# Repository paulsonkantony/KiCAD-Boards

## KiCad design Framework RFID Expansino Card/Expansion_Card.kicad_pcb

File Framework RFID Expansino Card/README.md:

# RFID Reader Expansion
This expansion will allow the user to add a RFID reader to the Framework Laptop (frame.work)

Framework Expansion Card Template is licensed under CC BY 4.0
- https://github.com/FrameworkComputer/ExpansionCards

USB RFID Reader schematic is released by Sparkfun under CC BY-SA 3.0
- https://github.com/sparkfun/RFID_USB_Reader/tree/V_1.8

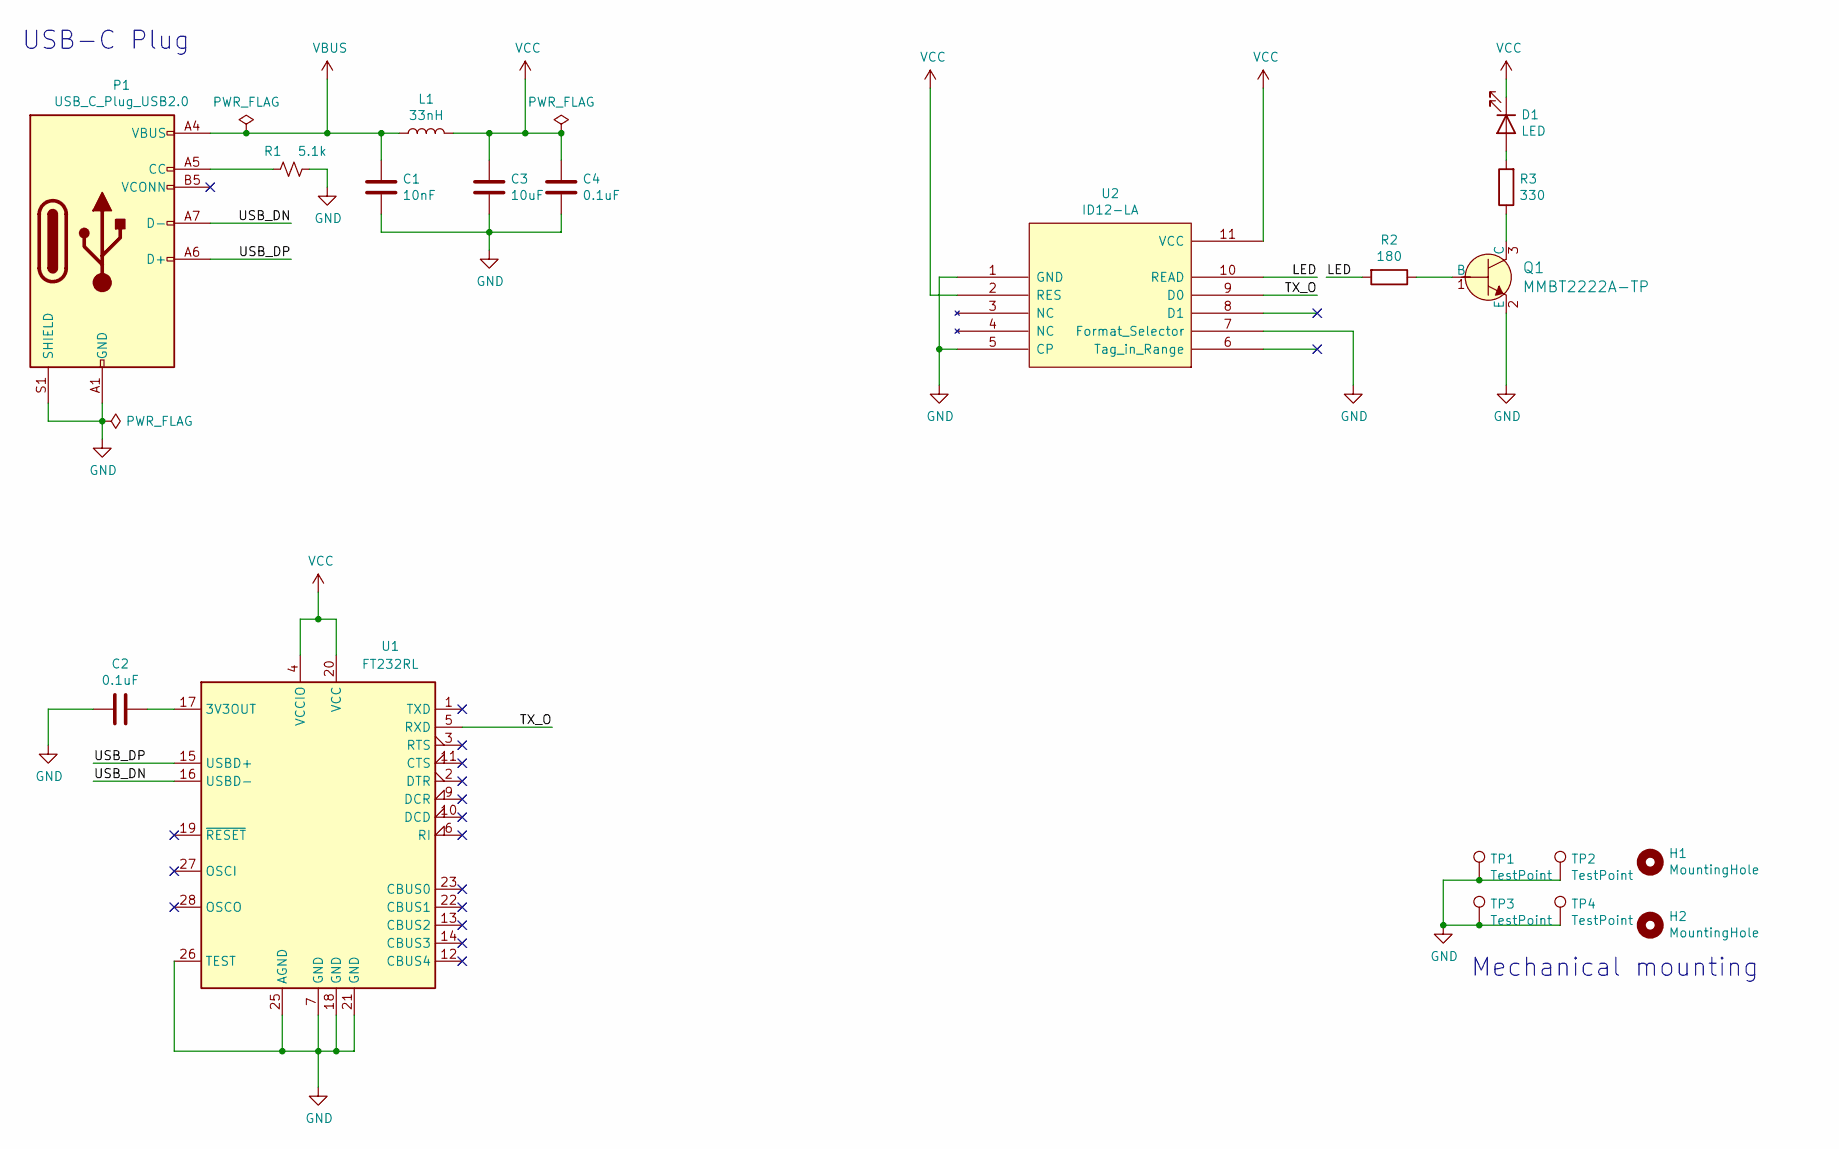
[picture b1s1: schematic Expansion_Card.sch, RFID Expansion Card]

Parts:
C1: 10nF; C_0805_2012Metric_Pad1.18x1.45mm_HandSolder
C2, C4: 0.1uF; C_0805_2012Metric_Pad1.18x1.45mm_HandSolder
C3: 10uF; C_0805_2012Metric_Pad1.18x1.45mm_HandSolder
D1: LED; LED_0805_2012Metric_Pad1.15x1.40mm_HandSolder
H1, H2: MountingHole; MountingHole_2.2mm_M2
L1: 33nH; L_0805_2012Metric_Pad1.15x1.40mm_HandSolder
P1: USB_C_Plug_USB2.0; USB_C_Plug_Molex_105444
Q1: MMBT2222A-TP; SOT-23-3; MPN MMBT2222A-TP; Digi-Key_PN MMBT2222ATPMSCT-ND
R1: 5.1k; R_0805_2012Metric_Pad1.20x1.40mm_HandSolder
R2: 180; R_0805_2012Metric_Pad1.20x1.40mm_HandSolder
R3: 330; R_0805_2012Metric_Pad1.20x1.40mm_HandSolder
TP1, TP2, TP3, TP4: TestPoint; TestPoint_Pad_1.5x1.5mm
U1: FT232RL; SSOP-28_5.3x10.2mm_P0.65mm
U2: ID12-LA; ID-12LA

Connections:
/LED: R2.2, U2.10 (READ)
/TX_O: U1.5 (RXD), U2.9 (D0)
/USB_DN: P1.A7 (D-), U1.16 (USBD-)
/USB_DP: P1.A6 (D+), U1.15 (USBD+)
GND: C1.2, C2.2, C3.2, C4.2, P1.A1 (GND), P1.A12 (GND), P1.B1 (GND), P1.B12 (GND), P1.S1 (SHIELD), Q1.2 (E), R1.2, TP1.1, TP2.1, TP3.1, TP4.1, U1.7 (GND), U1.18 (GND), U1.21 (GND), U1.25 (AGND), U1.26 (TEST), U2.1 (GND), U2.5 (CP), U2.7 (Format_Selector)
unnamed: C2.1, U1.17 (3V3OUT)
unnamed: D1.2 (A), R3.2
unnamed: P1.A5 (CC), R1.1
unnamed: Q1.1 (B), R2.1
unnamed: Q1.3 (C), R3.1
VBUS: C1.1, L1.1, P1.A4 (VBUS), P1.A9 (VBUS), P1.B4 (VBUS), P1.B9 (VBUS)
VCC: C3.1, C4.1, D1.1 (K), L1.2, U1.4 (VCCIO), U1.20 (VCC), U2.2 (RES), U2.11 (VCC)

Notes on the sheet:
USB-C Plug
Mechanical mounting

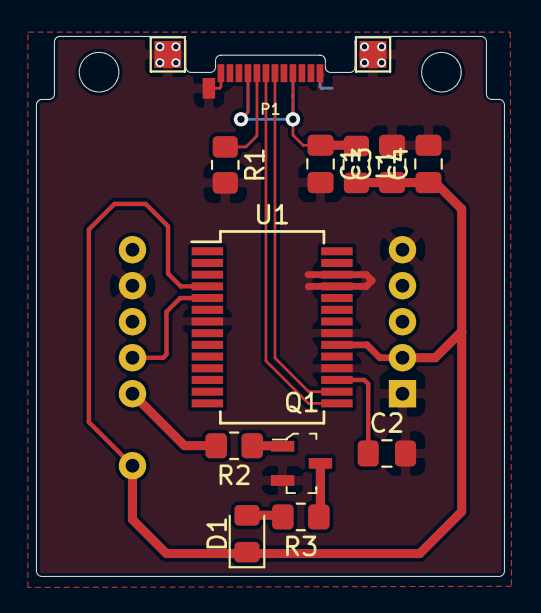
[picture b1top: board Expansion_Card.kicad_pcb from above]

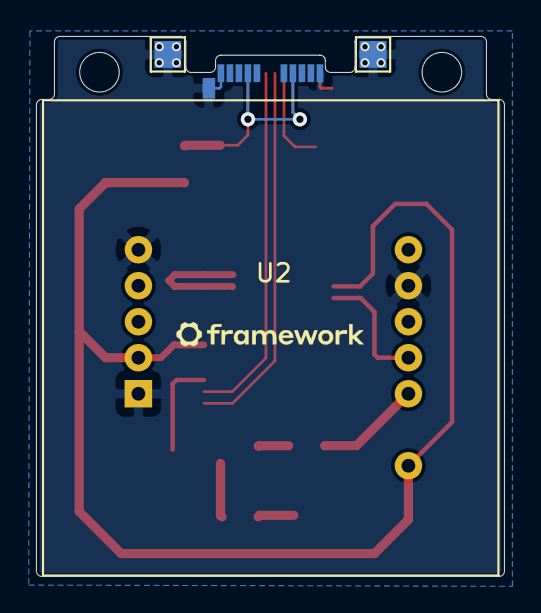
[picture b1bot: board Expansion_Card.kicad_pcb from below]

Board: 2 copper layers, 26.0 x 30.0 mm, 19 parts (3 on the bottom side), 12 nets.

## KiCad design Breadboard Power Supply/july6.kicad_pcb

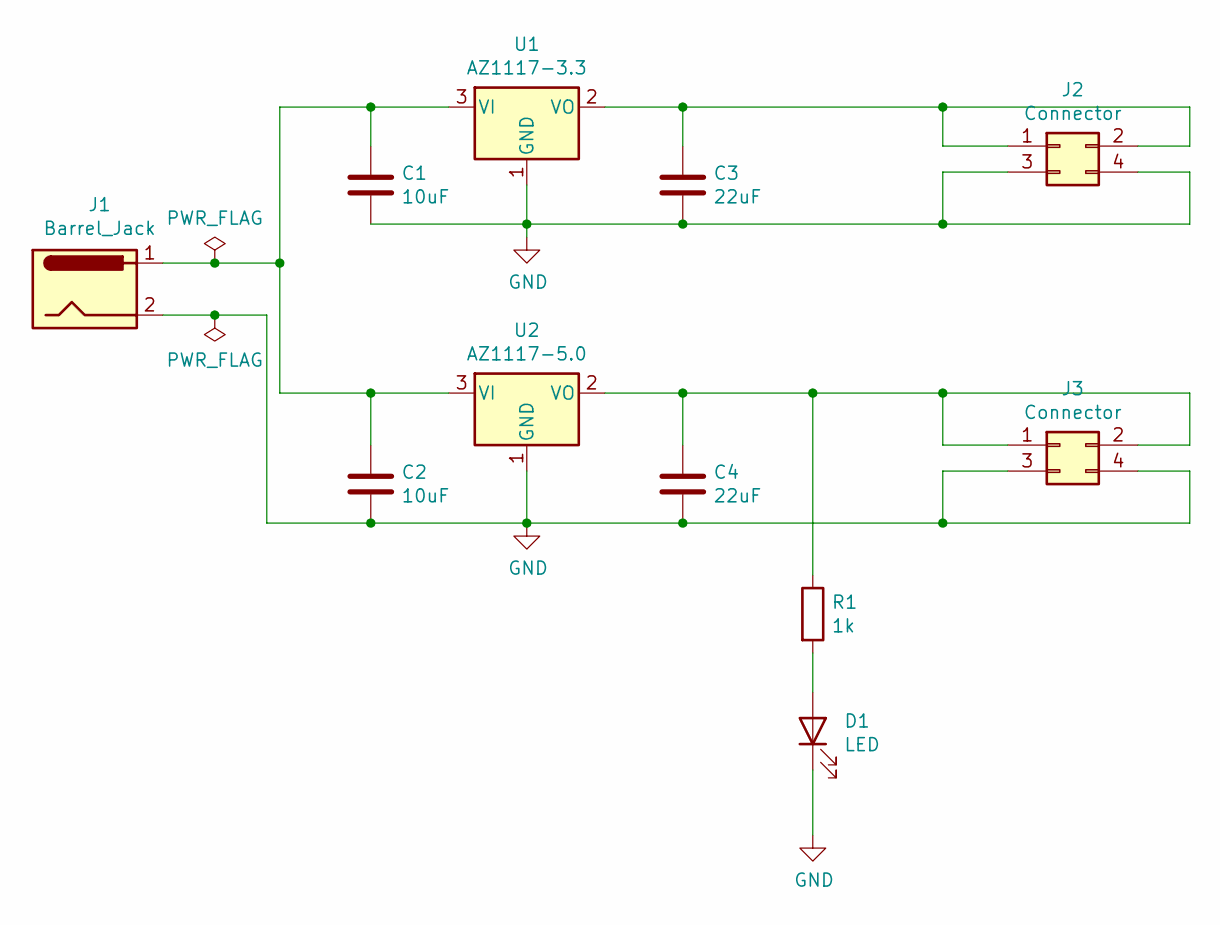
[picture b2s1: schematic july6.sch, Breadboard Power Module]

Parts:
C1, C2: 10uF; C_0805_2012Metric_Pad1.18x1.45mm_HandSolder
C3, C4: 22uF; C_0805_2012Metric_Pad1.18x1.45mm_HandSolder
D1: LED; LED_D3.0mm
J1: Barrel_Jack; BarrelJack_CUI_PJ-102AH_Horizontal
J2, J3: Connector; PinHeader_2x02_P2.54mm_Vertical
R1: 1k; R_0805_2012Metric_Pad1.20x1.40mm_HandSolder
U1: AZ1117-3.3; SOT-223-3_TabPin2
U2: AZ1117-5.0; SOT-223-3_TabPin2

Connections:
GND: C1.2, C2.2, C3.2, C4.2, D1.1 (K), J1.2, J2.3, J2.4, J3.3, J3.4, U1.1 (GND), U2.1 (GND)
unnamed: C1.1, C2.1, J1.1, U1.3 (VI), U2.3 (VI)
unnamed: C3.1, J2.1, J2.2, U1.2 (VO)
unnamed: C4.1, J3.1, J3.2, R1.1, U2.2 (VO)
unnamed: D1.2 (A), R1.2

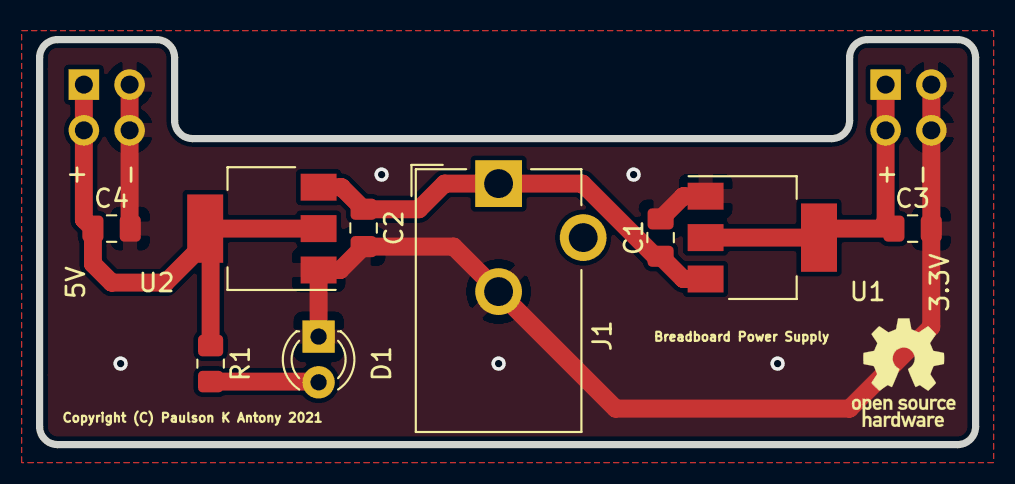
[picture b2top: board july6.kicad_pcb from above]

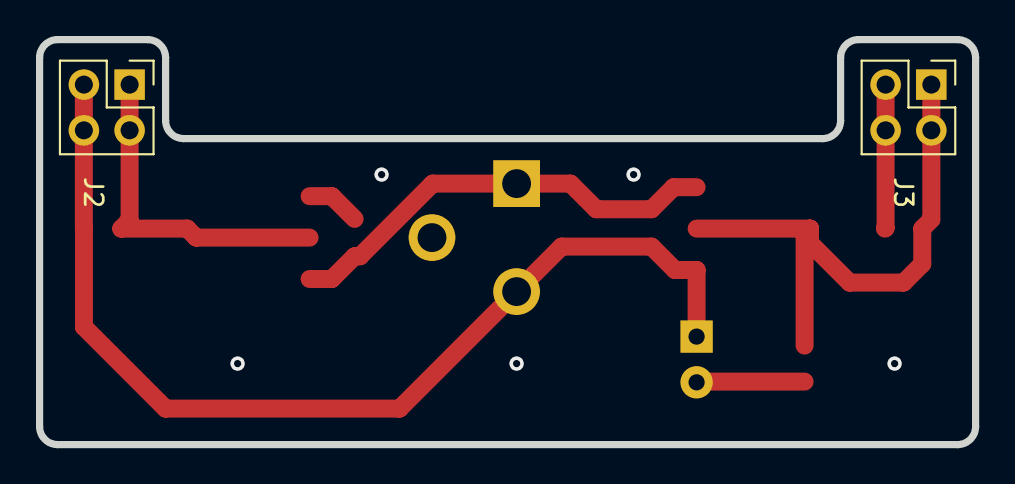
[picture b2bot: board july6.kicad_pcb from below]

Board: 2 copper layers, 52.0 x 22.5 mm, 11 parts (2 on the bottom side), 5 nets.

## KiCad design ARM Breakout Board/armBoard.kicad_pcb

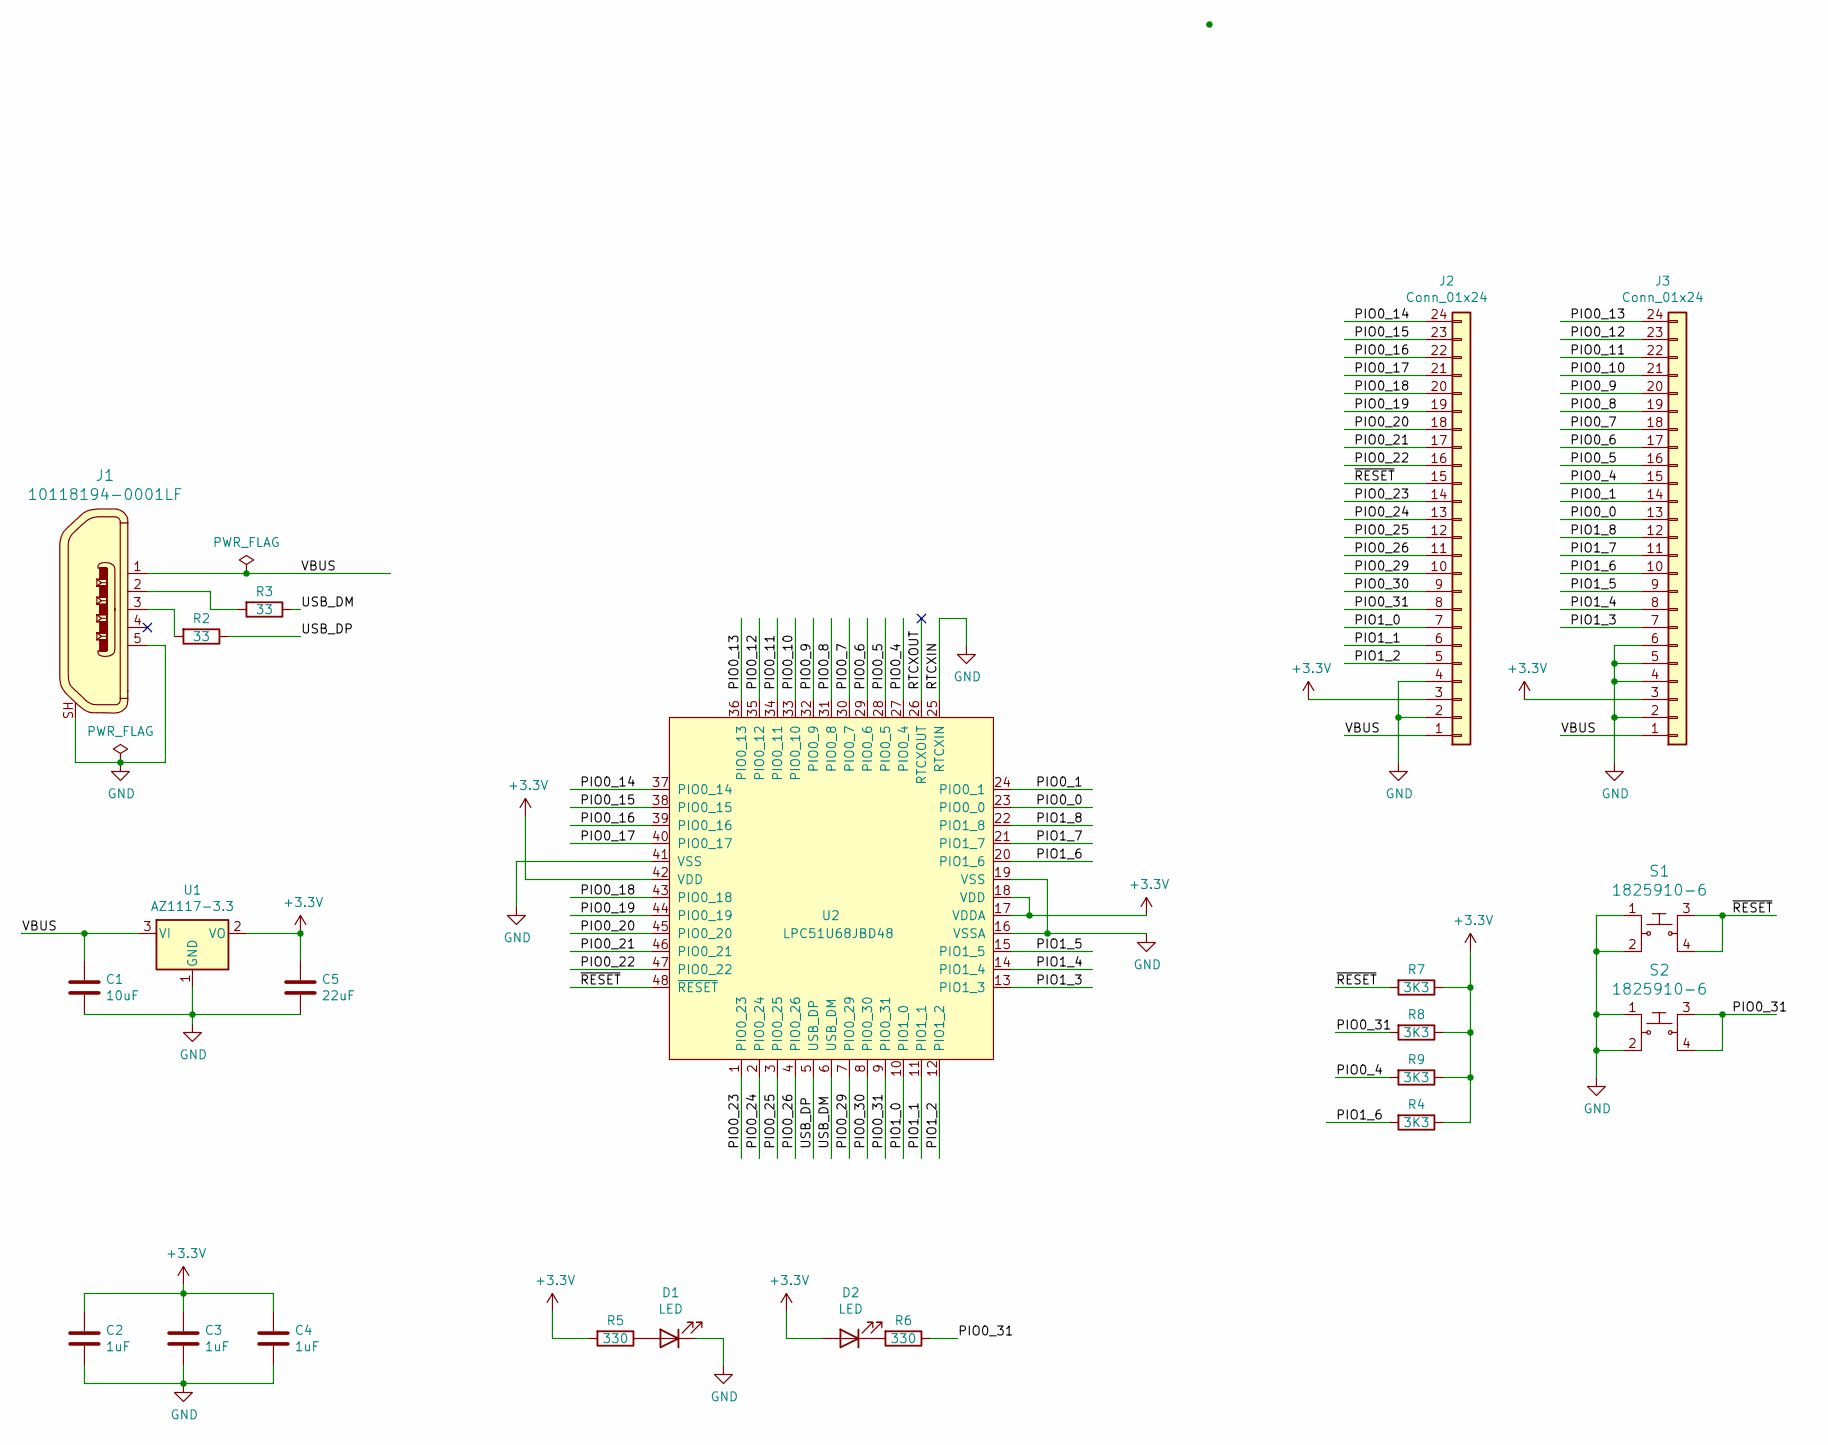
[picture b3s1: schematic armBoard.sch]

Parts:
C1: 10uF; C_0805_2012Metric_Pad1.18x1.45mm_HandSolder
C2, C3, C4: 1uF; C_0805_2012Metric_Pad1.18x1.45mm_HandSolder
C5: 22uF; C_0805_2012Metric_Pad1.18x1.45mm_HandSolder
D1, D2: LED; LED_0805_2012Metric_Pad1.15x1.40mm_HandSolder
J1: 10118194-0001LF; USB_Micro_B_Female_10118194-0001LF; MPN 10118194-0001LF; Digi-Key_PN 609-4618-1-ND
J2, J3: Conn_01x24; PinHeader_1x24_P2.54mm_Vertical
R2, R3: 33; R_0805_2012Metric_Pad1.20x1.40mm_HandSolder
R4, R7, R8, R9: 3K3; R_0805_2012Metric_Pad1.20x1.40mm_HandSolder
R5, R6: 330; R_0805_2012Metric_Pad1.20x1.40mm_HandSolder
S1, S2: 1825910-6; Switch_Tactile_THT_6x6mm; MPN 1825910-6; Digi-Key_PN 450-1650-ND
U1: AZ1117-3.3; SOT-223-3_TabPin2
U2: LPC51U68JBD48; LQFP-48_7x7mm_P0.5mm

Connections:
+3V3: C2.1, C3.1, C4.1, C5.1, D2.2 (A), J2.3, J3.3, R4.1, R5.2, R7.1, R8.1, R9.1, U1.2 (VO), U2.17 (VDDA), U2.18 (VDD), U2.42 (VDD)
/PIO0_0: J3.13, U2.23 (PIO0_0)
/PIO0_1: J3.14, U2.24 (PIO0_1)
/PIO0_4: J3.15, R9.2, U2.27 (PIO0_4)
/PIO0_5: J3.16, U2.28 (PIO0_5)
/PIO0_6: J3.17, U2.29 (PIO0_6)
/PIO0_7: J3.18, U2.30 (PIO0_7)
/PIO0_8: J3.19, U2.31 (PIO0_8)
/PIO0_9: J3.20, U2.32 (PIO0_9)
/PIO0_10: J3.21, U2.33 (PIO0_10)
/PIO0_11: J3.22, U2.34 (PIO0_11)
/PIO0_12: J3.23, U2.35 (PIO0_12)
/PIO0_13: J3.24, U2.36 (PIO0_13)
/PIO0_14: J2.24, U2.37 (PIO0_14)
/PIO0_15: J2.23, U2.38 (PIO0_15)
/PIO0_16: J2.22, U2.39 (PIO0_16)
/PIO0_17: J2.21, U2.40 (PIO0_17)
/PIO0_18: J2.20, U2.43 (PIO0_18)
/PIO0_19: J2.19, U2.44 (PIO0_19)
/PIO0_20: J2.18, U2.45 (PIO0_20)
/PIO0_21: J2.17, U2.46 (PIO0_21)
/PIO0_22: J2.16, U2.47 (PIO0_22)
/PIO0_23: J2.14, U2.1 (PIO0_23)
/PIO0_24: J2.13, U2.2 (PIO0_24)
/PIO0_25: J2.12, U2.3 (PIO0_25)
/PIO0_26: J2.11, U2.4 (PIO0_26)
/PIO0_29: J2.10, U2.7 (PIO0_29)
/PIO0_30: J2.9, U2.8 (PIO0_30)
/PIO0_31: J2.8, R6.1, R8.2, S2.3, S2.4, U2.9 (PIO0_31)
/PIO1_0: J2.7, U2.10 (PIO1_0)
/PIO1_1: J2.6, U2.11 (PIO1_1)
/PIO1_2: J2.5, U2.12 (PIO1_2)
/PIO1_3: J3.7, U2.13 (PIO1_3)
/PIO1_4: J3.8, U2.14 (PIO1_4)
/PIO1_5: J3.9, U2.15 (PIO1_5)
/PIO1_6: J3.10, R4.2, U2.20 (PIO1_6)
/PIO1_7: J3.11, U2.21 (PIO1_7)
/PIO1_8: J3.12, U2.22 (PIO1_8)
/RTCXOUT: U2.26 (RTCXOUT)
/USB_DM: R3.1, U2.6 (USB_DM)
/USB_DP: R2.1, U2.5 (USB_DP)
/VBUS: C1.1, J1.1, J2.1, J3.1, U1.3 (VI)
/~RESET~: J2.15, R7.2, S1.3, S1.4, U2.48 (~RESET~)
GND: C1.2, C2.2, C3.2, C4.2, C5.2, D1.1 (K), J1.5, J1.SH, J2.2, J2.4, J3.2, J3.4, J3.5, J3.6, S1.1, S1.2, S2.1, S2.2, U1.1 (GND), U2.16 (VSSA), U2.19 (VSS), U2.25 (RTCXIN), U2.41 (VSS)
unnamed: D1.2 (A), R5.1
unnamed: D2.1 (K), R6.2
unnamed: J1.2, R3.2
unnamed: J1.3, R2.2

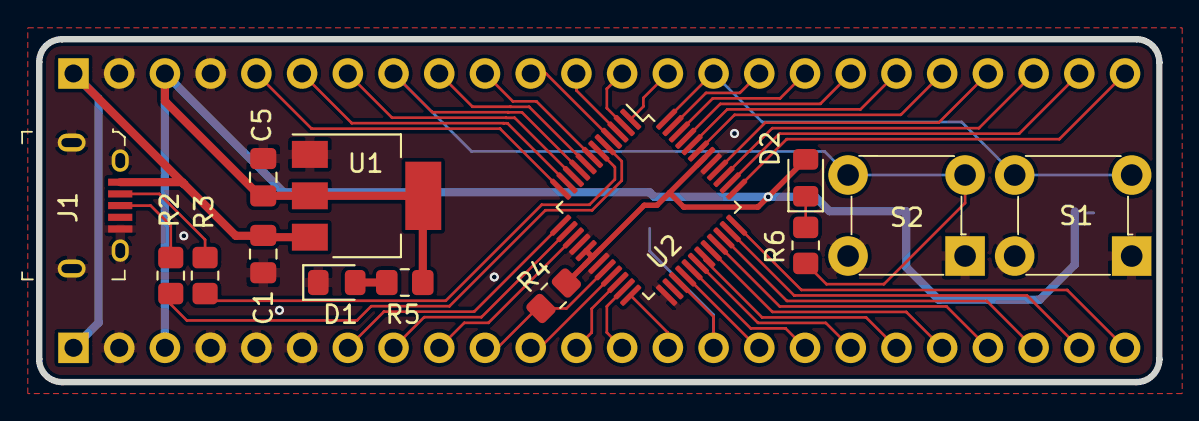
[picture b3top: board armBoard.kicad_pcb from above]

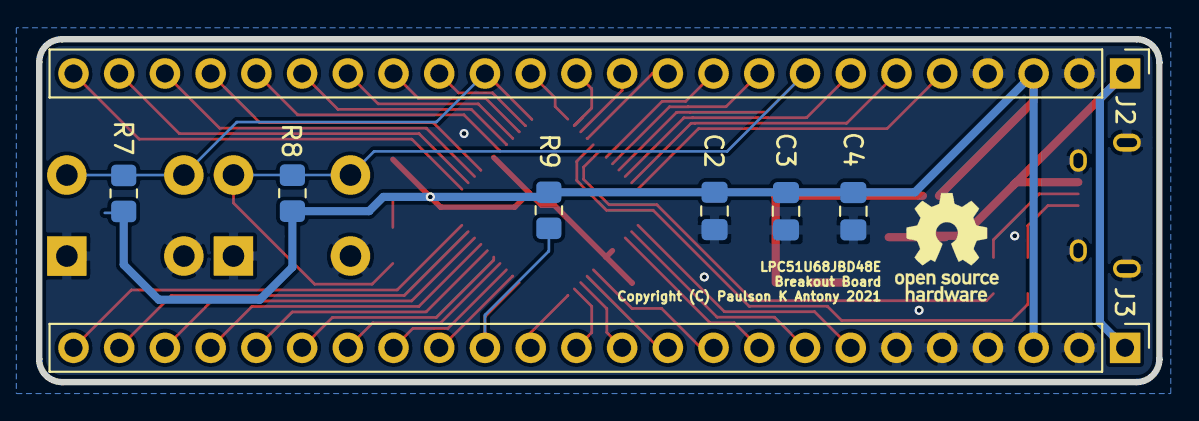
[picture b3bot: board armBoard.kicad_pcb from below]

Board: 2 copper layers, 62.2 x 19.1 mm, 22 parts (8 on the bottom side), 47 nets.

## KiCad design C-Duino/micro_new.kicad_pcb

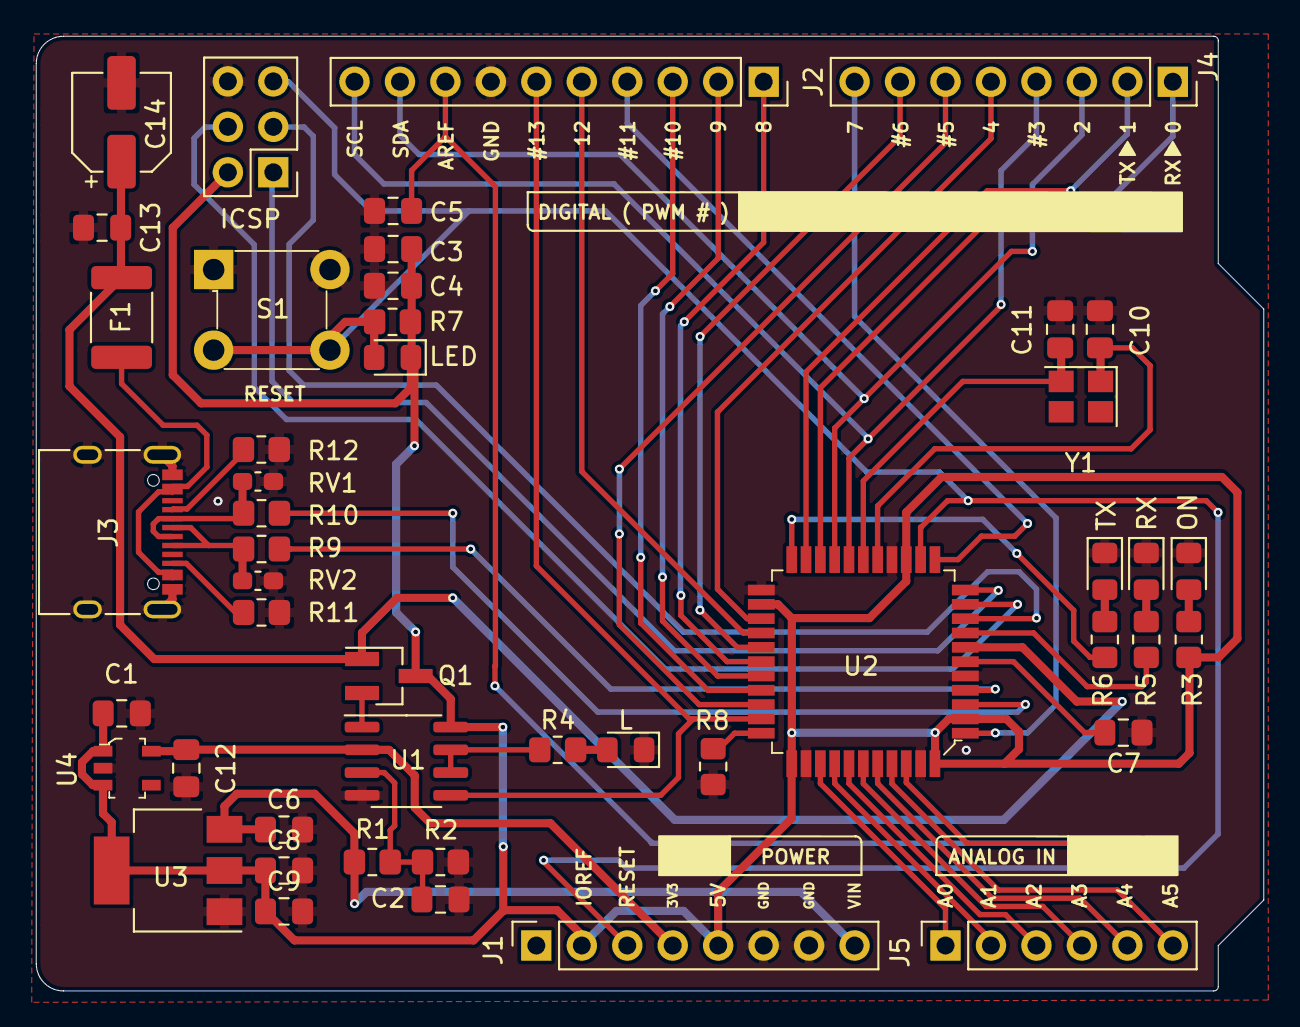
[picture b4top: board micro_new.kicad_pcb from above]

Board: 2 copper layers, 68.6 x 53.3 mm, 47 parts (0 on the bottom side), 50 nets.

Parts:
C1, C2, C3, C4, C5, C13: 100n; C_0805_2012Metric_Pad1.18x1.45mm_HandSolder
C6, C8: 10uF; C_0805_2012Metric_Pad1.18x1.45mm_HandSolder
C7, C9, C12: 1uF; C_0805_2012Metric_Pad1.18x1.45mm_HandSolder
C10, C11: 22pF; C_0805_2012Metric_Pad1.18x1.45mm_HandSolder
C14: 22uF; CP_Elec_5x3
F1: Fuse; Fuse_1812_4532Metric_Pad1.30x3.40mm_HandSolder
ICSP: Conn_02x03_Odd_Even; PinHeader_2x03_P2.54mm_Vertical
J1, J4: Conn_01x08_Female; PinSocket_1x08_P2.54mm_Vertical
J2: Conn_01x10_Female; PinSocket_1x10_P2.54mm_Vertical
J3: USB_C_Receptacle_USB2.0; USB_C_Receptacle_XKB_U262-16XN-4BVC11
J5: Conn_01x06_Female; PinSocket_1x06_P2.54mm_Vertical
L: L; LED_0805_2012Metric_Pad1.15x1.40mm_HandSolder
LED: LED; LED_0805_2012Metric_Pad1.15x1.40mm_HandSolder
ON: ON; LED_0805_2012Metric_Pad1.15x1.40mm_HandSolder
Q1: Q_PMOS_DGS; SOT-23_Handsoldering
R1, R2, R8: 10K; R_0805_2012Metric_Pad1.20x1.40mm_HandSolder
R3, R4, R5, R6: 1K; R_0805_2012Metric_Pad1.20x1.40mm_HandSolder
R7: R; R_0805_2012Metric_Pad1.20x1.40mm_HandSolder
R9, R10: 22; R_0805_2012Metric_Pad1.20x1.40mm_HandSolder
R11, R12: 5K1; R_0805_2012Metric_Pad1.20x1.40mm_HandSolder
RV1, RV2: Varistor; C_0603_1608Metric_Pad1.08x0.95mm_HandSolder
RX: RX; LED_0805_2012Metric_Pad1.15x1.40mm_HandSolder
S1: 1825910-6; Switch_Tactile_THT_6x6mm
TX: TX; LED_0805_2012Metric_Pad1.15x1.40mm_HandSolder
U1: LMV358; SOIC-8_3.9x4.9mm_P1.27mm
U2: ATMEGA32U4-AU; TQFP-44_10x10mm
U3: NCP1117-5.0_SOT223; SOT-223-3_TabPin2
U4: LP2985-33DBVR; SOT-753
Y1: 16Mhz; Crystal_SMD_3225-4Pin_3.2x2.5mm

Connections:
+3V3: C12.1, J1.4, U1.2, U4.5
+5V: C1.1, C3.1, C4.1, C8.1, C9.1, ICSP.2, J1.2, J1.5, LED.1, Q1.3, R3.1, R7.1, U1.8, U2.2, U2.14, U2.24, U2.34, U2.44, U3.2, U4.1, U4.3
/A0: J5.1, U2.36
/A1: J5.2, U2.37
/A2: J5.3, U2.38
/A3: J5.4, U2.39
/A4: J5.5, U2.40
/A5: J5.6, U2.41
/AREF: C5.1, J2.8, U2.42
/D0: J4.1, U2.20
/D1: J4.2, U2.21
/D2: J2.9, J4.3, U2.19
/D3: J2.10, J4.4, U2.18
/D4: J4.5, U2.25
/D5: J4.6, U2.31
/D6: J4.7, U2.27
/D7: J4.8, U2.1
/HWB: R8.1, U2.33
/IO8: J2.1, U2.28
/IO9: J2.2, U2.29
/IO10: J2.3, U2.30
/IO11: J2.4, U2.12
/IO12: J2.5, U2.26
/IO13: J2.6, U1.5, U2.32
/MISO: ICSP.1, U2.11
/MOSI: ICSP.4, U2.10
/RD+: R9.1, U2.4
/RD-: R10.1, U2.3
/RESET: ICSP.5, J1.3, LED.2, R7.2, S1.3, S1.4, U2.13
/RXLED: R5.1, U2.8
/SCK: ICSP.3, U2.9
/TXLED: R6.1, U2.22
/VIN: C6.1, J1.8, R1.1, U3.3
GND: C1.2, C2.2, C3.2, C4.2, C5.2, C6.2, C7.2, C8.2, C9.2, C10.2, C11.2, C12.2, C13.2, C14.2, ICSP.6, J1.6, J1.7, J2.7, J3.A1, J3.A12, J3.B1, J3.B12, J3.S1, L.1, ON.1, R2.2, R8.2, R11.1, R12.1, RV1.2, RV2.2, RX.1, S1.1, S1.2, TX.1, U1.4, U2.5, U2.15, U2.23, U2.35, U2.43, U3.1, U4.2
unnamed: C2.1, R1.2, R2.1, U1.3
unnamed: C7.1, U2.6
unnamed: C10.1, U2.16, Y1.1
unnamed: C11.1, U2.17, Y1.2
unnamed: ON.2, R3.2
unnamed: L.2, R4.2
unnamed: R5.2, RX.2
unnamed: R6.2, TX.2
unnamed: F1.1, J3.A4, J3.A9, J3.B4, J3.B9
unnamed: J3.A5, R12.2
unnamed: J3.A6, J3.B6, R9.2, RV2.1
unnamed: J3.A7, J3.B7, R10.2, RV1.1
unnamed: J3.B5, R11.2
unnamed: Q1.2, U1.1
unnamed: R4.1, U1.6, U1.7
VDD: C13.1, C14.1, F1.2, Q1.1, U2.7

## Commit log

2021-07-17 Initial Upload

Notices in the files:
ARM Breakout Board/armBoard.kicad_pcb:
Copyright (C) Paulson K Antony 2021
Framework RFID Expansino Card/Expansion_Card.kicad_pcb:
This work is licensed under a Creative Commons Attribution 4.0 International License
